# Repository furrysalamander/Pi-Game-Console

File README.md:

# Pi-Game-Console
 
A CM3+ Lite based handheld game console.

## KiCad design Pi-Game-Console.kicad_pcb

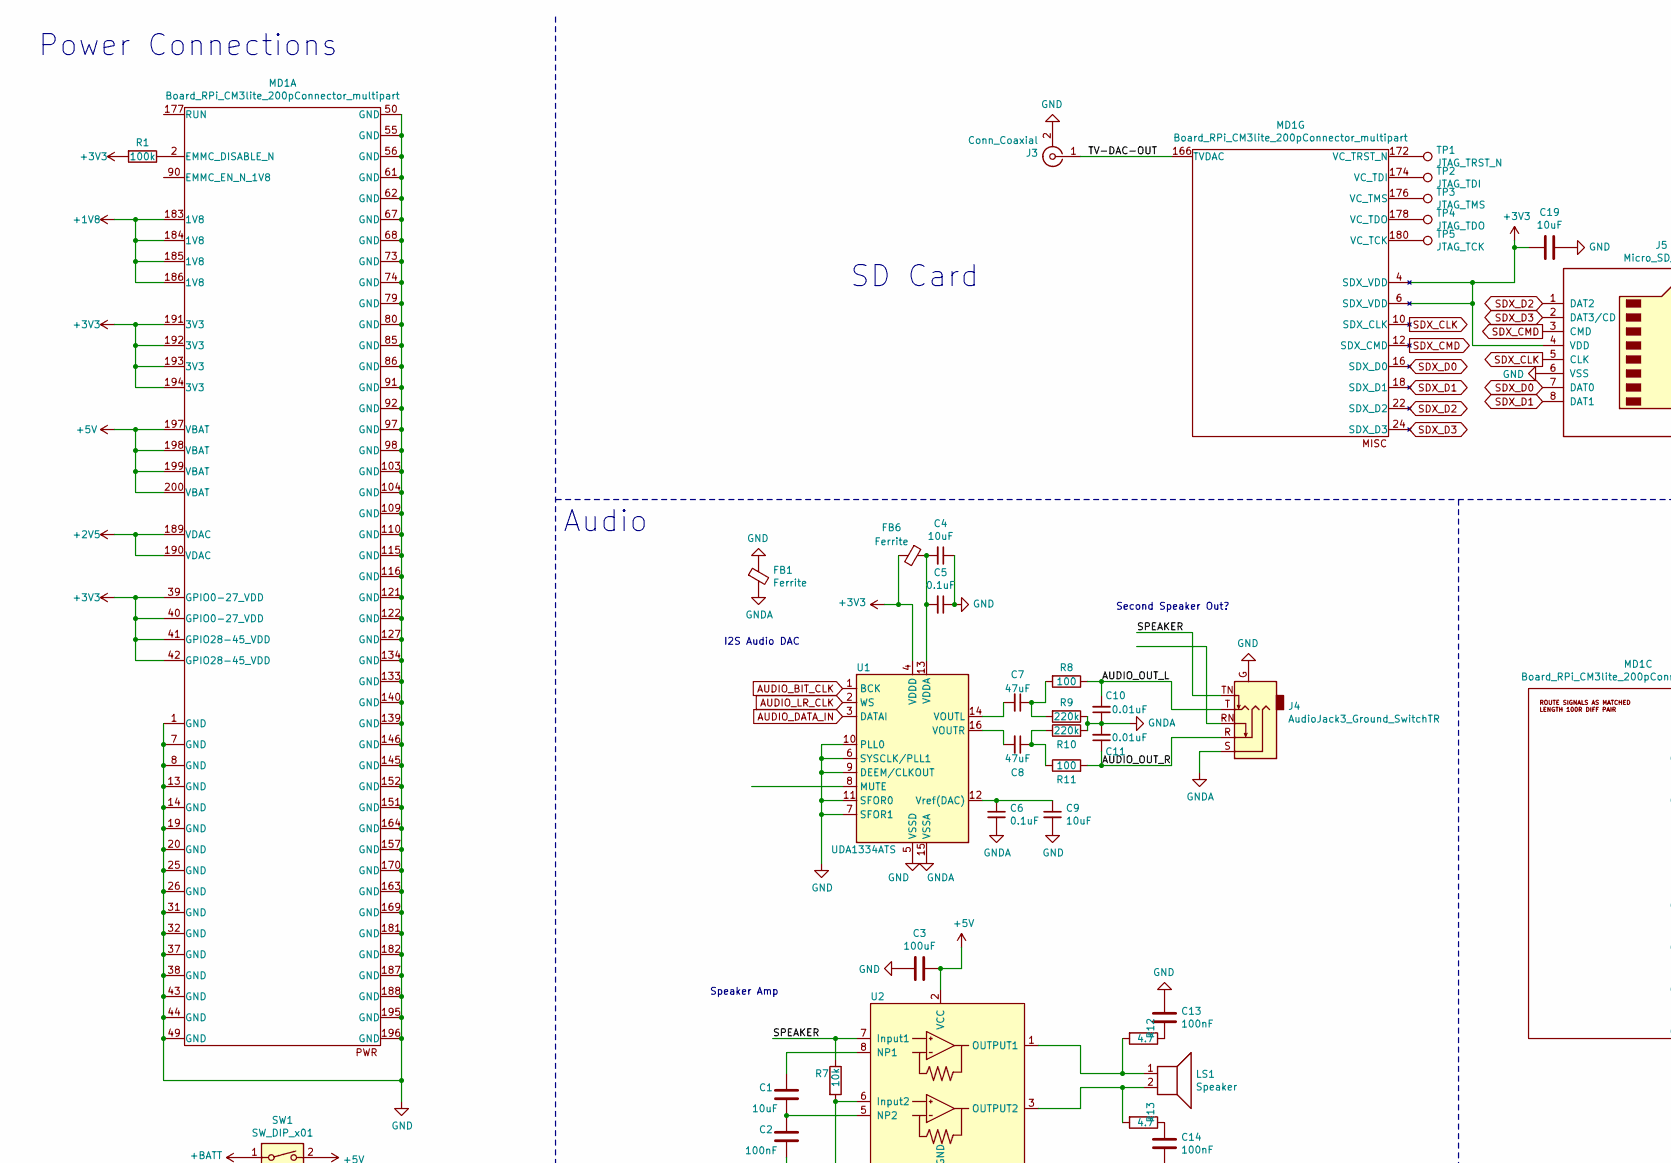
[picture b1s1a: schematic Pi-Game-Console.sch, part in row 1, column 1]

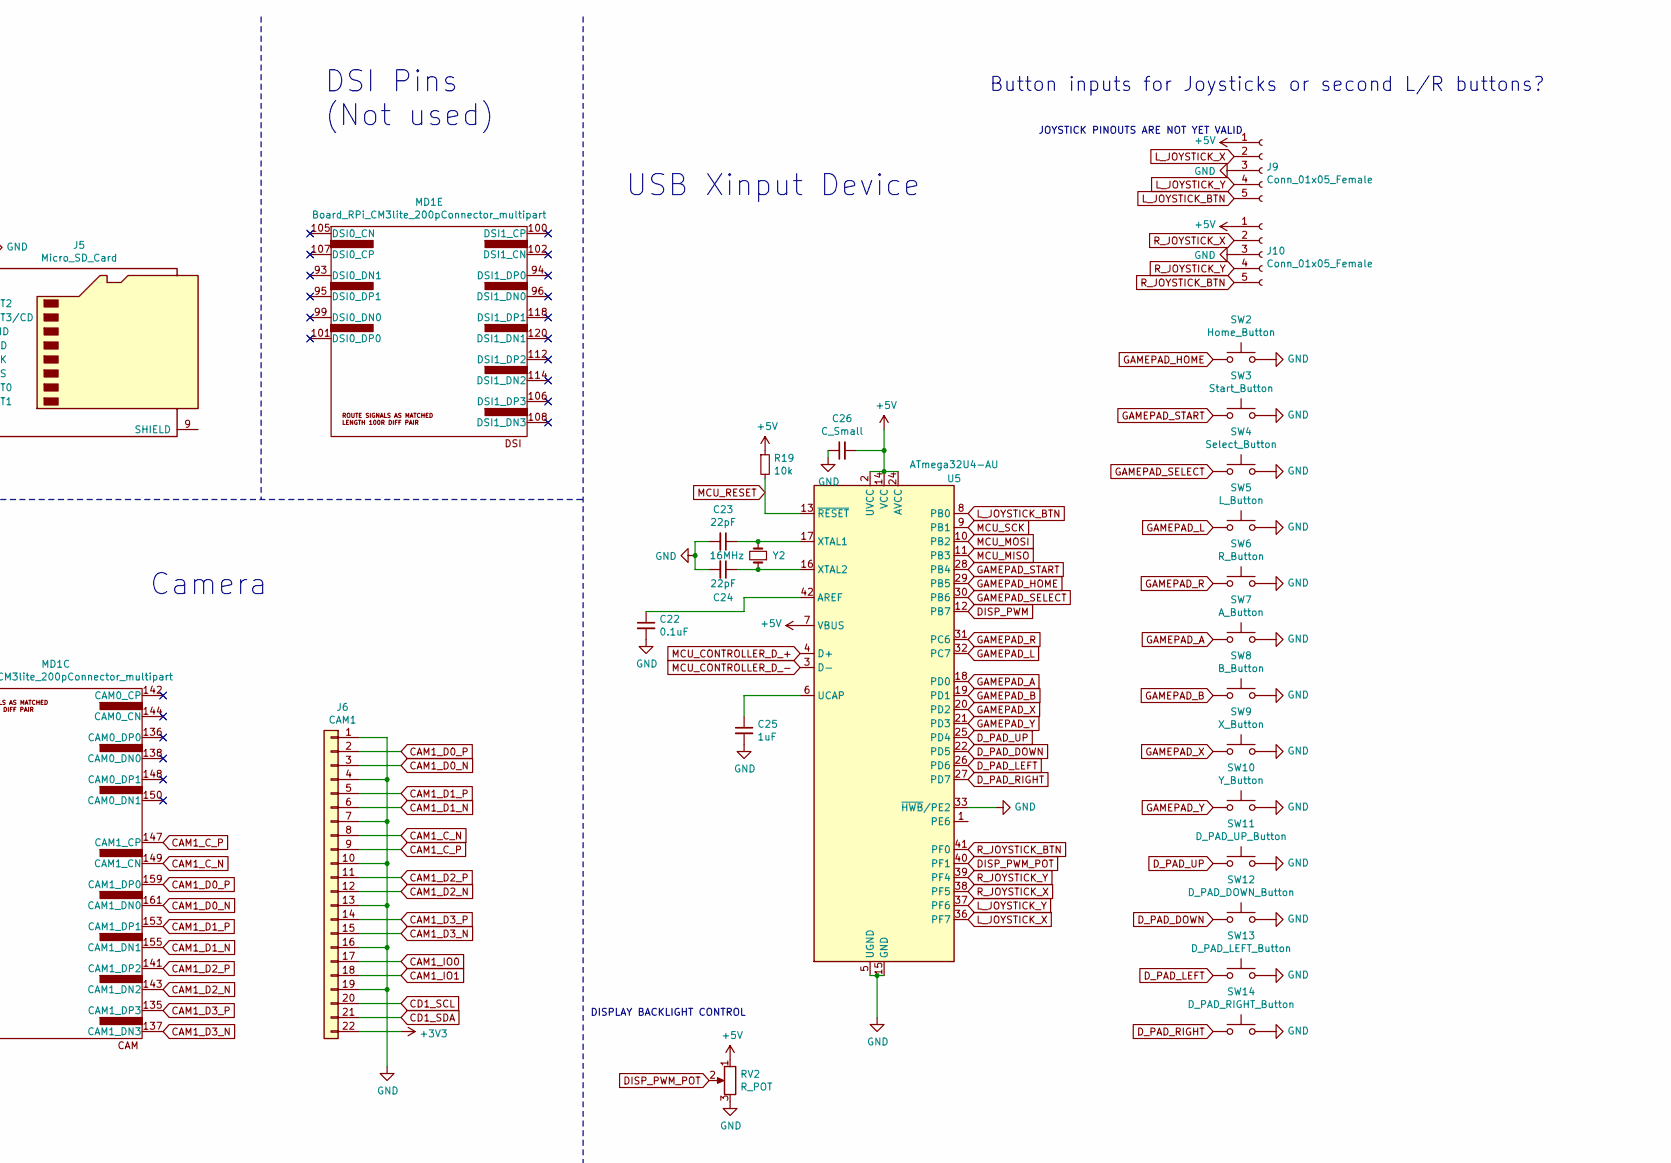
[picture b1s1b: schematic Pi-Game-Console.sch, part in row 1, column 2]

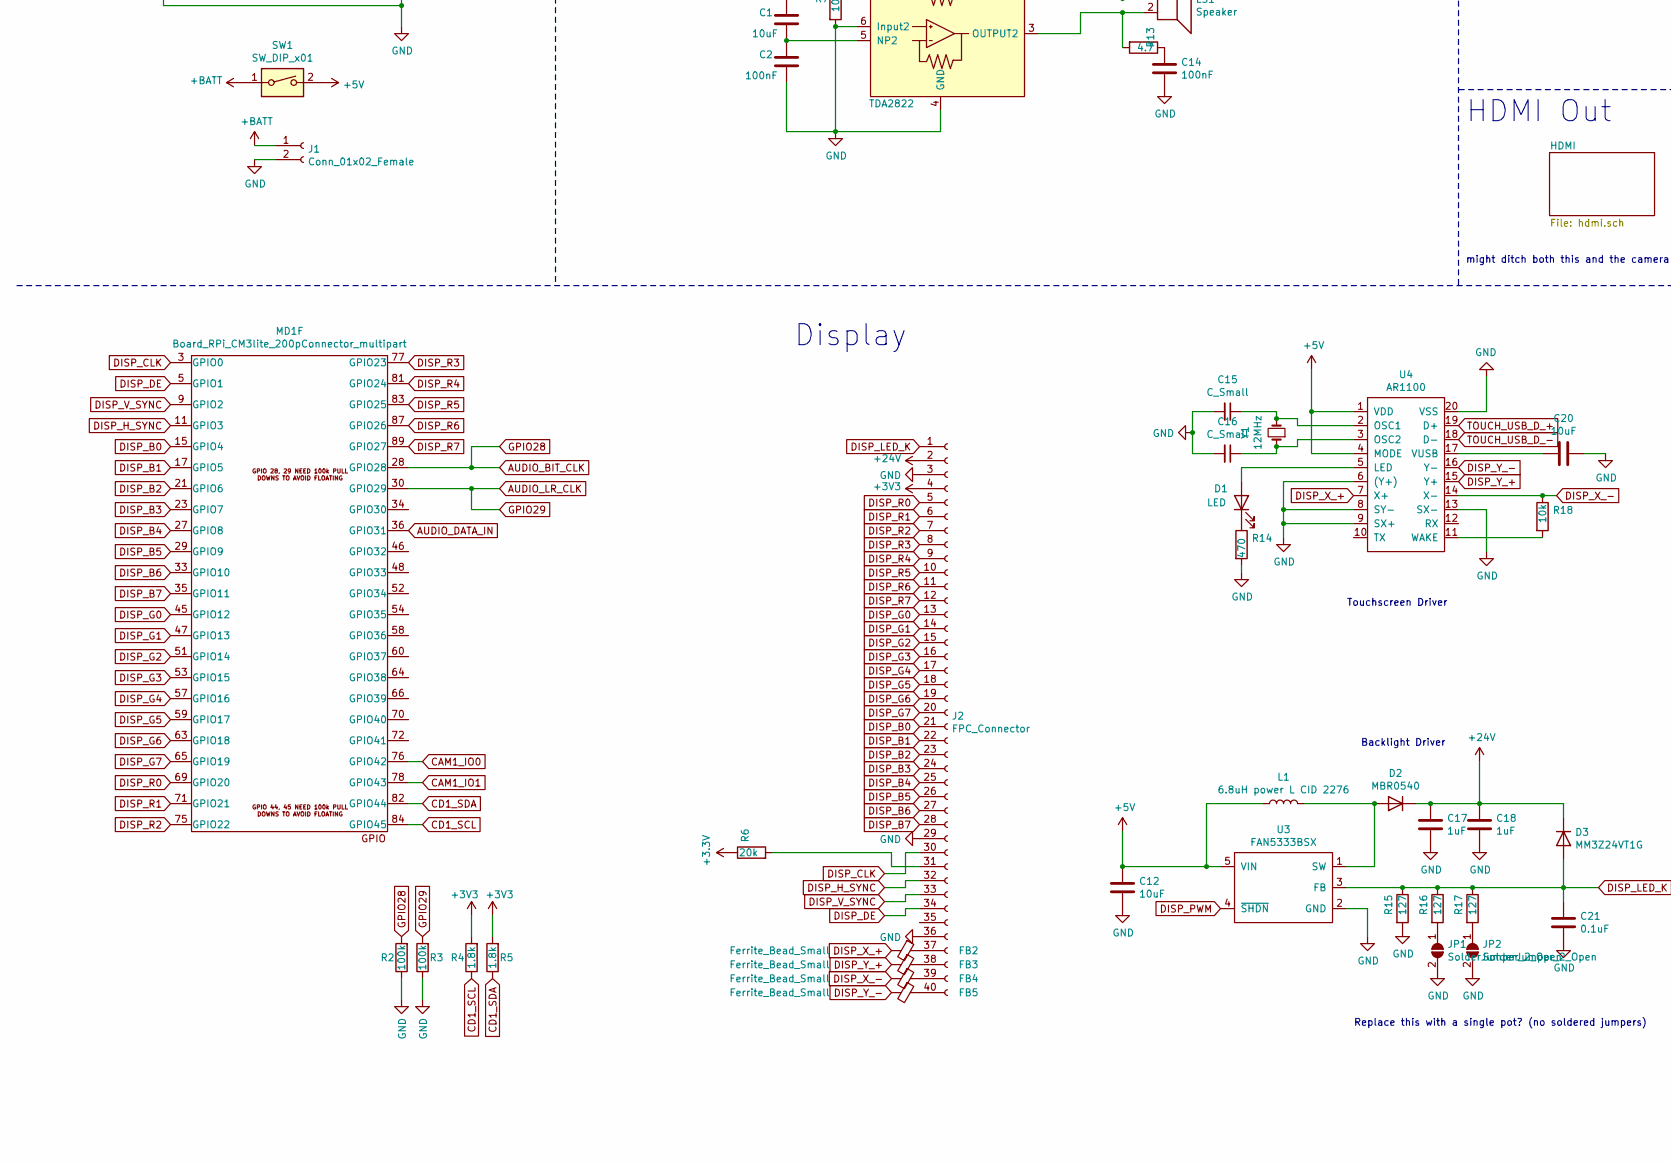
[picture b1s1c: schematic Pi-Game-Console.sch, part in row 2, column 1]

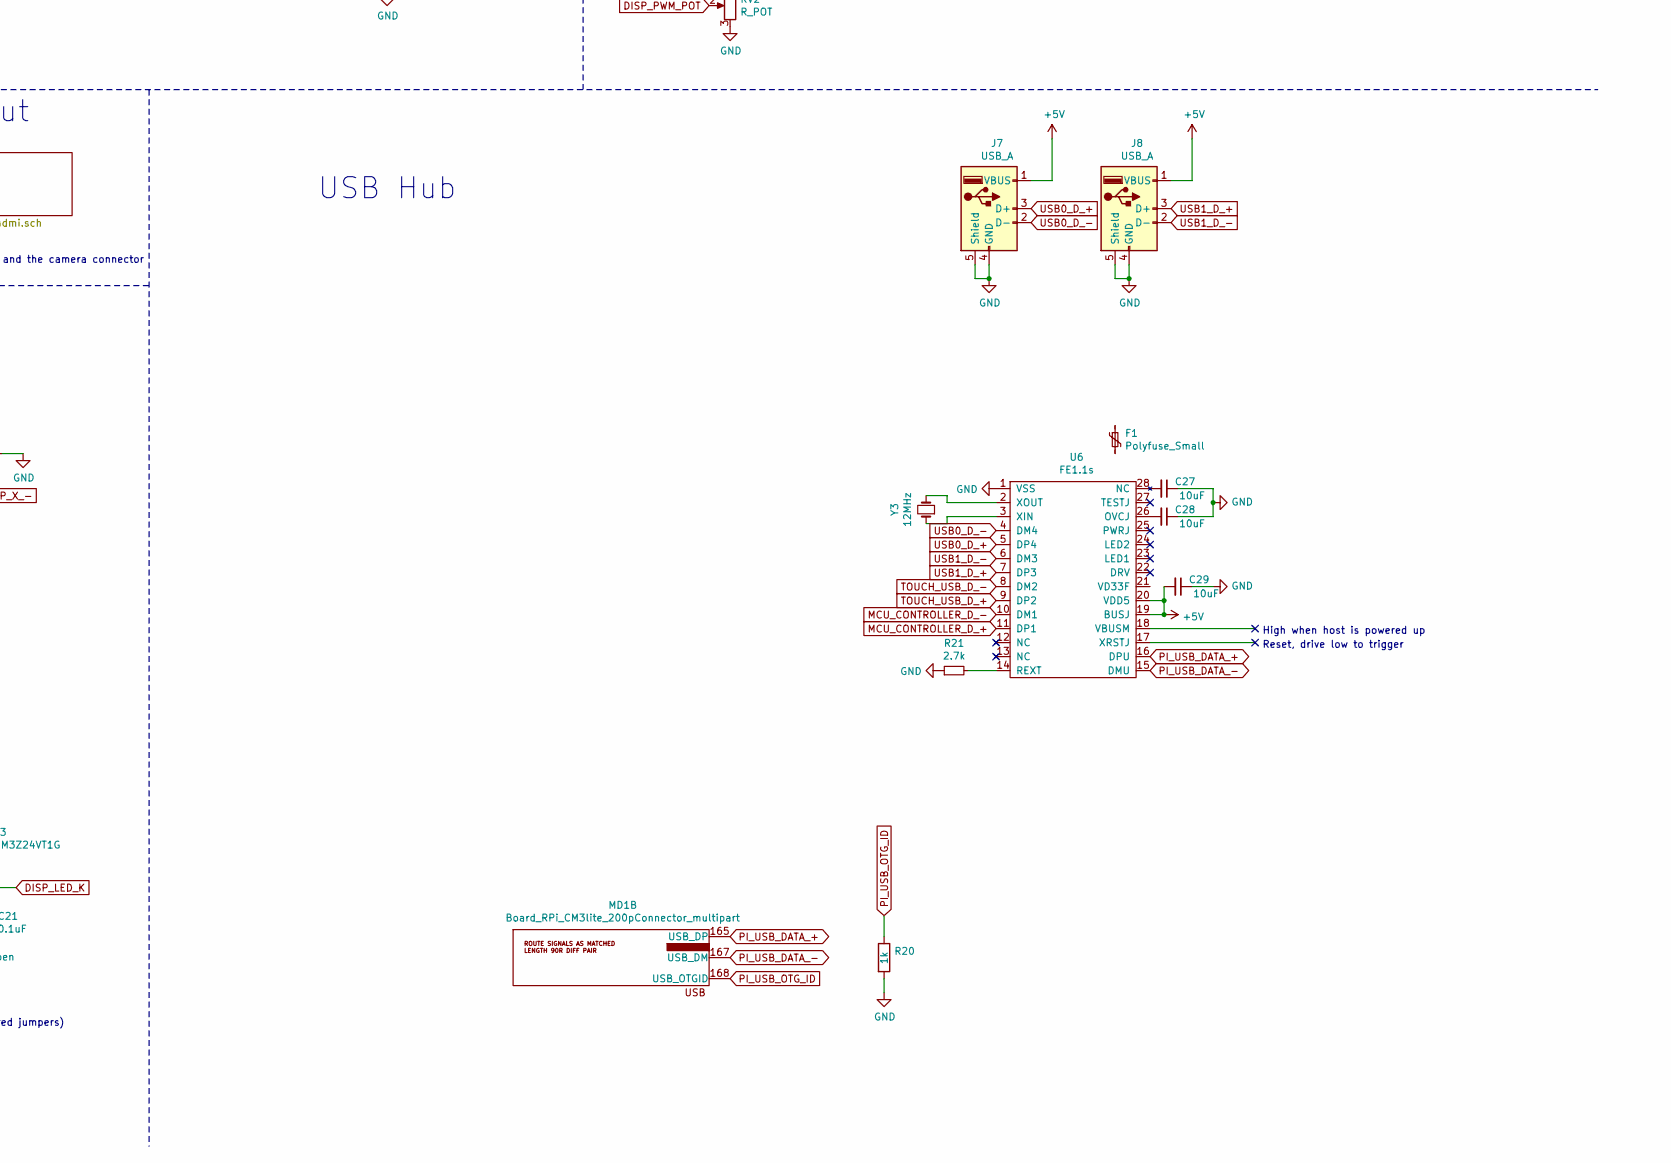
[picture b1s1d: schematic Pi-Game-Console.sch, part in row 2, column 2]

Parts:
C1, C4, C9, C12, C19, C20, C27, C28, C29: 10uF; C_0805_2012Metric
C2, C13, C14: 100nF; C_0805_2012Metric
C3: 100uF; C_0805_2012Metric
C5, C6, C21, C22: 0.1uF; C_0805_2012Metric
C7, C8: 47uF; C_0805_2012Metric
C10, C11: 0.01uF; C_0805_2012Metric
C15, C16, C26: C_Small; C_0805_2012Metric
C17, C18, C25: 1uF; C_0805_2012Metric
C23, C24: 22pF; C_0805_2012Metric
D1: LED; LED_0805_2012Metric
D2: MBR0540; D_0805_2012Metric
D3: MM3Z24VT1G; D_0805_2012Metric
F1: Polyfuse_Small; Littelfuse_PolyZen-LS
FB1, FB6: Ferrite; L_0805_2012Metric
FB2, FB3, FB4, FB5: Ferrite_Bead_Small; L_0805_2012Metric
J1: Conn_01x02_Female; PinHeader_1x02_P2.54mm_Vertical
J2: FPC_Connector; Hirose_FH12-40S-0.5SH_1x40-1MP_P0.50mm_Horizontal
J3: Conn_Coaxial; SMB_Jack_Vertical
J4: AudioJack3_Ground_SwitchTR; Jack_3.5mm_PJ311_Horizontal
J5: Micro_SD_Card; microSD_HC_Molex_104031-0811
J6: CAM1; Hirose_FH12-22S-0.5SH_1x22-1MP_P0.50mm_Horizontal
J7, J8: USB_A; USB_A_Stewart_SS-52100-001_Horizontal
J9, J10: Conn_01x05_Female; Molex_200528-0050_1x05-1MP_P1.00mm_Horizontal
JP1, JP2: SolderJumper_2_Open; SolderJumper-2_P1.3mm_Open_TrianglePad1.0x1.5mm
L1: 6.8uH power L CID 2276; L_Bourns-SRU1028_10.0x10.0mm
LS1: Speaker; Molex_CLIK-Mate_502382-0270_1x02-1MP_P1.25mm_Vertical
MD1: Board_RPi_CM3lite_200pConnector_multipart; Conn_TE-DDR2-SODIMM-0.6-200P-doublesided
R1, R2, R3: 100k; R_0805_2012Metric
R4, R5: 1.8k; R_0805_2012Metric
R6: 20k; R_0805_2012Metric
R7, R18, R19: 10k; R_0805_2012Metric
R8, R11: 100; R_0805_2012Metric
R9, R10: 220k; R_0805_2012Metric
R12, R13: 4.7; R_0805_2012Metric
R14: 470; R_0805_2012Metric
R15, R16, R17: 127; R_0805_2012Metric
R20: 1k; R_0805_2012Metric
R21: 2.7k; R_0805_2012Metric
RV2: R_POT; Potentiometer_Bourns_3269P_Horizontal
SW1: SW_DIP_x01; SW_CuK_OS102011MA1QN1_SPDT_Angled
SW2: Home_Button; SW_PUSH_6mm_H5mm
SW3: Start_Button; SW_PUSH_6mm_H5mm
SW4: Select_Button; SW_PUSH_6mm_H5mm
SW5: L_Button; SW_PUSH_6mm_H5mm
SW6: R_Button; SW_PUSH_6mm_H5mm
SW7: A_Button; SW_PUSH_6mm_H5mm
SW8: B_Button; SW_PUSH_6mm_H5mm
SW9: X_Button; SW_PUSH_6mm_H5mm
SW10: Y_Button; SW_PUSH_6mm_H5mm
SW11: D_PAD_UP_Button; SW_PUSH_6mm_H5mm
SW12: D_PAD_DOWN_Button; SW_PUSH_6mm_H5mm
SW13: D_PAD_LEFT_Button; SW_PUSH_6mm_H5mm
SW14: D_PAD_RIGHT_Button; SW_PUSH_6mm_H5mm
TP1: JTAG_TRST_N; TestPoint_Pad_D1.5mm
TP2: JTAG_TDI; TestPoint_Pad_D1.5mm
TP3: JTAG_TMS; TestPoint_Pad_D1.5mm
TP4: JTAG_TDO; TestPoint_Pad_D1.5mm
TP5: JTAG_TCK; TestPoint_Pad_D1.5mm
U1: UDA1334ATS; SSOP-16_4.4x5.2mm_P0.65mm
U2: TDA2822; SOIC-8_3.9x4.9mm_P1.27mm
U3: FAN5333BSX; SO-5_4.4x3.6mm_P1.27mm
U4: AR1100; SOIC-20W_7.5x12.8mm_P1.27mm
U5: ATmega32U4-AU; TQFP-44_10x10mm_P0.8mm
U6: FE1.1s; SOIC-28W_7.5x17.9mm_P1.27mm
Y1, Y3: 12MHz; Crystal_SMD_ECS_CSM3X-2Pin_7.6x4.1mm
Y2: 16MHz; Crystal_SMD_ECS_CSM3X-2Pin_7.6x4.1mm

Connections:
+1V8: MD1.183 (1V8), MD1.184 (1V8), MD1.185 (1V8), MD1.186 (1V8)
+2V5: MD1.189 (VDAC), MD1.190 (VDAC)
+5V: C3.2, C12.1, C26.2, C29.2, J7.1 (VBUS), J8.1 (VBUS), J9.1, J10.1, L1.1, MD1.197 (VBAT), MD1.198 (VBAT), MD1.199 (VBAT), MD1.200 (VBAT), R19.1, RV2.1, SW1.2, U2.2 (VCC), U3.5 (VIN), U4.1 (VDD), U4.4 (MODE), U5.2 (UVCC), U5.7 (VBUS), U5.14 (VCC), U5.24 (AVCC), U5.34 (VCC), U5.44 (AVCC), U6.19 (BUSJ), U6.20 (VDD5); also elsewhere on the board
+24V: C17.1, C18.1, D2.1 (K), D3.1 (K), J2.2
+BATT: J1.1, SW1.1
/AUDIO_OUT_L: C10.2, J4.T, R8.1
/AUDIO_OUT_R: C11.1, J4.R, R11.2
/SPEAKER: J4.TN, R7.1, U2.7 (Input1)
/TV-DAC-OUT: J3.1 (In), MD1.166 (TVDAC)
AUDIO_BIT_CLK: MD1.28 (GPIO28), R2.2, U1.1 (BCK)
AUDIO_DATA_IN: MD1.36 (GPIO31), U1.3 (DATAI)
AUDIO_LR_CLK: MD1.30 (GPIO29), R3.2, U1.2 (WS)
CAM1_C_N: J6.8, MD1.149 (CAM1_CN)
CAM1_C_P: J6.9, MD1.147 (CAM1_CP)
CAM1_D0_N: J6.3, MD1.161 (CAM1_DN0)
CAM1_D0_P: J6.2, MD1.159 (CAM1_DP0)
CAM1_D1_N: J6.6, MD1.155 (CAM1_DN1)
CAM1_D1_P: J6.5, MD1.153 (CAM1_DP1)
CAM1_D2_N: J6.12, MD1.143 (CAM1_DN2)
CAM1_D2_P: J6.11, MD1.141 (CAM1_DP2)
CAM1_D3_N: J6.15, MD1.137 (CAM1_DN3)
CAM1_D3_P: J6.14, MD1.135 (CAM1_DP3)
CAM1_IO0: J6.17, MD1.76 (GPIO42)
CAM1_IO1: J6.18, MD1.78 (GPIO43)
CD1_SCL: J6.20, MD1.84 (GPIO45), R4.1
CD1_SDA: J6.21, MD1.82 (GPIO44), R5.1
DISP_B0: J2.21, MD1.15 (GPIO4)
DISP_B1: J2.22, MD1.17 (GPIO5)
DISP_B2: J2.23, MD1.21 (GPIO6)
DISP_B3: J2.24, MD1.23 (GPIO7)
DISP_B4: J2.25, MD1.27 (GPIO8)
DISP_B5: J2.26, MD1.29 (GPIO9)
DISP_B6: J2.27, MD1.33 (GPIO10)
DISP_B7: J2.28, MD1.35 (GPIO11)
DISP_CLK: J2.30, MD1.3 (GPIO0)
DISP_DE: J2.34, MD1.5 (GPIO1)
DISP_G0: J2.13, MD1.45 (GPIO12)
DISP_G1: J2.14, MD1.47 (GPIO13)
DISP_G2: J2.15, MD1.51 (GPIO14)
DISP_G3: J2.16, MD1.53 (GPIO15)
DISP_G4: J2.17, MD1.57 (GPIO16)
DISP_G5: J2.18, MD1.59 (GPIO17)
DISP_G6: J2.19, MD1.63 (GPIO18)
DISP_G7: J2.20, MD1.65 (GPIO19)
DISP_H_SYNC: J2.32, MD1.11 (GPIO3)
DISP_LED_K: C21.1, D3.2 (A), J2.1, R15.1, R16.1, R17.1, U3.3 (FB); also elsewhere on the board
DISP_PWM: U3.4 (~SHDN), U5.12 (PB7)
DISP_PWM_POT: RV2.2, U5.40 (PF1)
DISP_R0: J2.5, MD1.69 (GPIO20)
DISP_R1: J2.6, MD1.71 (GPIO21)
DISP_R2: J2.7, MD1.75 (GPIO22)
DISP_R3: J2.8, MD1.77 (GPIO23)
DISP_R4: J2.9, MD1.81 (GPIO24)
DISP_R5: J2.10, MD1.83 (GPIO25)
DISP_R6: J2.11, MD1.87 (GPIO26)
DISP_R7: J2.12, MD1.89 (GPIO27)
DISP_V_SYNC: J2.33, MD1.9 (GPIO2)
DISP_X_+: FB2.2, U4.7 (X+)
DISP_X_-: FB4.2, R18.1, U4.14 (X-)
DISP_Y_+: FB3.2, U4.15 (Y+)
DISP_Y_-: FB5.2, U4.16 (Y-)
D_PAD_DOWN: SW12.1, U5.22 (PD5)
D_PAD_LEFT: SW13.1, U5.26 (PD6)
D_PAD_RIGHT: SW14.1, U5.27 (PD7)
D_PAD_UP: SW11.1, U5.25 (PD4)
GAMEPAD_A: SW7.1, U5.18 (PD0)
GAMEPAD_B: SW8.1, U5.19 (PD1)
GAMEPAD_HOME: SW2.1, U5.29 (PB5)
GAMEPAD_L: SW5.1, U5.32 (PC7)
GAMEPAD_R: SW6.1, U5.31 (PC6)
GAMEPAD_SELECT: SW4.1, U5.30 (PB6)
GAMEPAD_START: SW3.1, U5.28 (PB4)
GAMEPAD_X: SW9.1, U5.20 (PD2)
GAMEPAD_Y: SW10.1, U5.21 (PD3)
GND: C2.2, C3.1, C4.1, C5.1, C9.2, C12.2, C13.1, C14.2, C15.2, C16.2, C17.2, C18.2, C19.2, C20.1, C21.2, C22.2, C23.2, C24.2, C25.2, C26.1, C27.1, C28.1, C29.1, FB1.1, J1.2, J2.3, J2.29, J2.36, J3.2 (Ext), J4.G, J5.6 (VSS), J6.1, J6.4, J6.7, J6.10, J6.13, J6.16, J6.19, J7.4 (GND), J7.5 (Shield), J8.4 (GND), J8.5 (Shield), J9.3, J10.3, JP1.2 (B), JP2.2 (B), MD1.1 (GND), MD1.7 (GND), MD1.8 (GND), MD1.13 (GND), MD1.14 (GND), MD1.19 (GND), MD1.20 (GND), MD1.25 (GND), MD1.26 (GND), MD1.31 (GND), MD1.32 (GND), MD1.37 (GND), MD1.38 (GND), MD1.43 (GND), MD1.44 (GND), MD1.49 (GND), MD1.50 (GND), MD1.55 (GND), MD1.56 (GND), MD1.61 (GND), MD1.62 (GND), MD1.67 (GND), MD1.68 (GND), MD1.73 (GND), MD1.74 (GND), MD1.79 (GND), MD1.80 (GND), MD1.85 (GND), MD1.86 (GND), MD1.91 (GND), MD1.92 (GND), MD1.97 (GND), MD1.98 (GND), MD1.103 (GND), MD1.104 (GND), MD1.109 (GND), MD1.110 (GND), MD1.115 (GND), MD1.116 (GND), MD1.121 (GND), MD1.122 (GND), MD1.127 (GND), MD1.133 (GND), MD1.134 (GND), MD1.139 (GND), MD1.140 (GND), MD1.145 (GND), MD1.146 (GND), MD1.151 (GND), MD1.152 (GND), MD1.157 (GND), MD1.163 (GND), MD1.164 (GND), MD1.169 (GND), MD1.170 (GND), MD1.181 (GND), MD1.182 (GND), MD1.187 (GND), MD1.188 (GND), MD1.195 (GND), MD1.196 (GND), R2.1, R3.1, R7.2, R14.2, R15.2, R20.2, R21.1, RV2.3, SW2.2, SW3.2, SW4.2, SW5.2, SW6.2, SW7.2, SW8.2, SW9.2, SW10.2, SW11.2, SW12.2, SW13.2, SW14.2, U1.5 (VSSD), U1.6 (SYSCLK/PLL1), U1.7 (SFOR1), U1.9 (DEEM/CLKOUT), U1.10 (PLL0), U1.11 (SFOR0), U2.4 (GND), U2.6 (Input2), U3.2 (GND), U4.6 ((Y+)), U4.8 (SY-), U4.9 (SX+), U4.13 (SX-), U4.20 (VSS), U5.5 (UGND), U5.15 (GND), U5.23 (GND), U5.33 (~HWB~/PE2), U5.35 (GND), U5.43 (GND), U6.1 (VSS); also elsewhere on the board
GNDA: C6.2, C10.1, C11.2, FB1.2, J4.S, R9.1, R10.2, U1.15 (VSSA)
L_JOYSTICK_BTN: J9.5, U5.8 (PB0)
L_JOYSTICK_X: J9.2, U5.36 (PF7)
L_JOYSTICK_Y: J9.4, U5.37 (PF6)
MCU_CONTROLLER_D_+: U5.4 (D+), U6.11 (DP1)
MCU_CONTROLLER_D_-: U5.3 (D-), U6.10 (DM1)
MCU_MISO: U5.11 (PB3)
MCU_MOSI: U5.10 (PB2)
MCU_RESET: R19.2, U5.13 (~RESET)
MCU_SCK: U5.9 (PB1)
unnamed: C1.1, U2.8 (NP1)
unnamed: C1.2, C2.1, U2.5 (NP2)
unnamed: C4.2, C5.2, FB6.1, U1.13 (VDDA)
unnamed: C6.1, C9.1, U1.12 (Vref(DAC))
unnamed: C7.1, R8.2, R9.2
unnamed: C7.2, U1.14 (VOUTL)
unnamed: C8.1, R10.1, R11.1
unnamed: C8.2, U1.16 (VOUTR)
unnamed: C13.2, R12.1
unnamed: C14.1, R13.1
unnamed: C15.1, U4.2 (OSC1), Y1.2
unnamed: C16.1, U4.3 (OSC2), Y1.1
unnamed: C20.2, U4.17 (VUSB)
unnamed: C22.1, U5.42 (AREF)
unnamed: C23.1, U5.17 (XTAL1), Y2.2
unnamed: C24.1, U5.16 (XTAL2), Y2.1
unnamed: C25.1, U5.6 (UCAP)
unnamed: C27.2, U6.28 (NC)
unnamed: C28.2, U6.26 (OVCJ)
unnamed 117: D1.1 (K), R14.1; also elsewhere on the board
unnamed 118: D1.2 (A), U4.5 (LED); also elsewhere on the board
unnamed: D2.2 (A), L1.2, U3.1 (SW)
unnamed: FB2.1, J2.37
unnamed: FB3.1, J2.38
unnamed: FB4.1, J2.39
unnamed: FB5.1, J2.40
unnamed: J2.31, R6.2
unnamed: JP1.1 (A), R16.2
unnamed 133: JP2.1 (A), R17.2; also elsewhere on the board
unnamed: LS1.1, R12.2, U2.1 (OUTPUT1)
unnamed: LS1.2, R13.2, U2.3 (OUTPUT2)
unnamed: MD1.2 (EMMC_DISABLE_N), R1.1
unnamed: MD1.172 (VC_TRST_N), TP1.1
unnamed: MD1.174 (VC_TDI), TP2.1
unnamed: MD1.176 (VC_TMS), TP3.1
unnamed: MD1.178 (VC_TDO), TP4.1
unnamed: MD1.180 (VC_TCK), TP5.1
unnamed: R18.2, U4.11 (WAKE)
unnamed: R21.2, U6.14 (REXT)
unnamed: U6.2 (XOUT), Y3.2
unnamed: U6.3 (XIN), Y3.1
PI_USB_DATA_+: MD1.165 (USB_DP), U6.16 (DPU)
PI_USB_DATA_-: MD1.167 (USB_DM), U6.15 (DMU)
PI_USB_OTG_ID: MD1.168 (USB_OTGID), R20.1
R_JOYSTICK_BTN: J10.5, U5.41 (PF0)
R_JOYSTICK_X: J10.2, U5.38 (PF5)
R_JOYSTICK_Y: J10.4, U5.39 (PF4)
SDX_CLK: J5.5 (CLK), MD1.10 (SDX_CLK)
SDX_CMD: J5.3 (CMD), MD1.12 (SDX_CMD)
SDX_D0: J5.7 (DAT0), MD1.16 (SDX_D0)
SDX_D1: J5.8 (DAT1), MD1.18 (SDX_D1)
SDX_D2: J5.1 (DAT2), MD1.22 (SDX_D2)
SDX_D3: J5.2 (DAT3/CD), MD1.24 (SDX_D3)
TOUCH_USB_D_+: U4.19 (D+), U6.9 (DP2)
TOUCH_USB_D_-: U4.18 (D-), U6.8 (DM2)
USB0_D_+: J7.3 (D+), U6.5 (DP4)
USB0_D_-: J7.2 (D-), U6.4 (DM4)
USB1_D_+: J8.3 (D+), U6.7 (DP3)
USB1_D_-: J8.2 (D-), U6.6 (DM3)

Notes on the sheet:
Reset, drive low to trigger
High when host is powered up
Audio
Replace this with a single pot? (no soldered jumpers)
Button inputs for Joysticks or second L/R buttons?
Power Connections
Display
SD Card
Camera
USB Hub
USB Xinput Device
DSI Pins (Not used)
HDMI Out
Touchscreen Driver
Backlight Driver
might ditch both this and the camera connector
Speaker Amp
I2S Audio DAC
Second Speaker Out?
JOYSTICK PINOUTS ARE NOT YET VALID
DISPLAY BACKLIGHT CONTROL

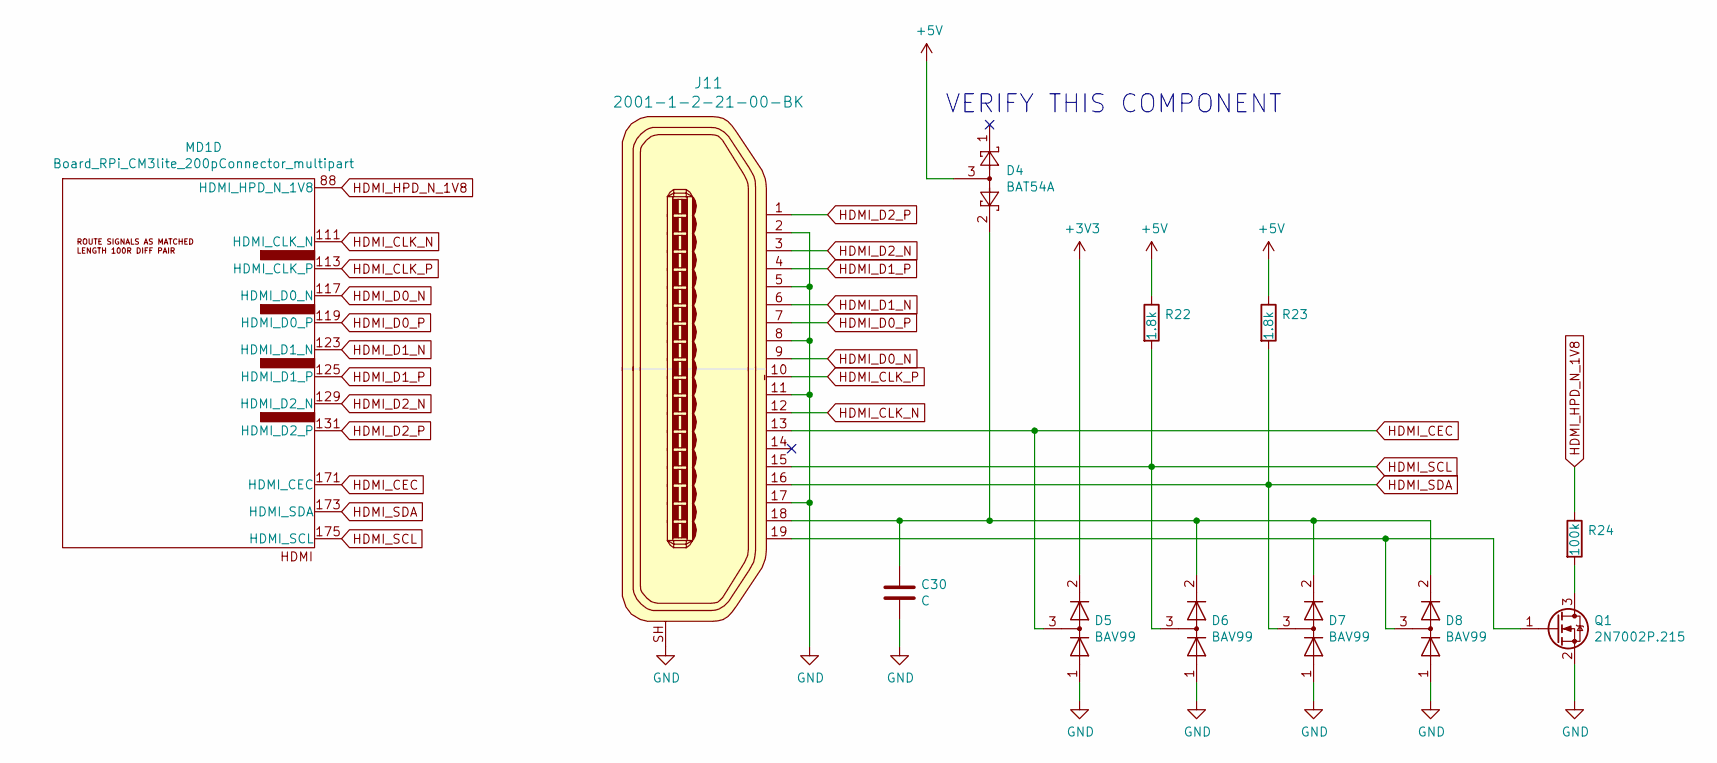
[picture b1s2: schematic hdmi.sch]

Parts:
C30: C; C_0805_2012Metric
D4: BAT54A; SOT-23
D5, D6, D7, D8: BAV99; SOT-23
J11: 2001-1-2-21-00-BK; HDMI_MOLEX_471510001; MPN 2001-1-2-21-00-BK; Digi-Key_PN 1175-1704-1-ND
MD1: Board_RPi_CM3lite_200pConnector_multipart; Conn_TE-DDR2-SODIMM-0.6-200P-doublesided
Q1: 2N7002P.215; SOT-23
R22, R23: 1.8k; R_0805_2012Metric
R24: 100k; R_0805_2012Metric

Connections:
+5V: D4.3, R22.1, R23.1; also elsewhere on the board
GND: C30.2, D5.1 (K), D6.1 (K), D7.1 (K), D8.1 (K), J11.2, J11.5, J11.8, J11.11, J11.17, J11.SH, Q1.2 (S); also elsewhere on the board
HDMI_CEC: D5.3 (K), J11.13, MD1.171 (HDMI_CEC)
HDMI_CLK_N: J11.12, MD1.111 (HDMI_CLK_N)
HDMI_CLK_P: J11.10, MD1.113 (HDMI_CLK_P)
HDMI_D0_N: J11.9, MD1.117 (HDMI_D0_N)
HDMI_D0_P: J11.7, MD1.119 (HDMI_D0_P)
HDMI_D1_N: J11.6, MD1.123 (HDMI_D1_N)
HDMI_D1_P: J11.4, MD1.125 (HDMI_D1_P)
HDMI_D2_N: J11.3, MD1.129 (HDMI_D2_N)
HDMI_D2_P: J11.1, MD1.131 (HDMI_D2_P)
HDMI_HPD_N_1V8: MD1.88 (HDMI_HPD_N_1V8), R24.1
HDMI_SCL: D6.3 (K), J11.15, MD1.175 (HDMI_SCL), R22.2
HDMI_SDA: D7.3 (K), J11.16, MD1.173 (HDMI_SDA), R23.2
unnamed: C30.1, D4.2, D6.2 (A), D7.2 (A), D8.2 (A), J11.18
unnamed: D8.3 (K), J11.19, Q1.1 (G)
unnamed: Q1.3 (D), R24.2

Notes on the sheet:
VERIFY THIS COMPONENT

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
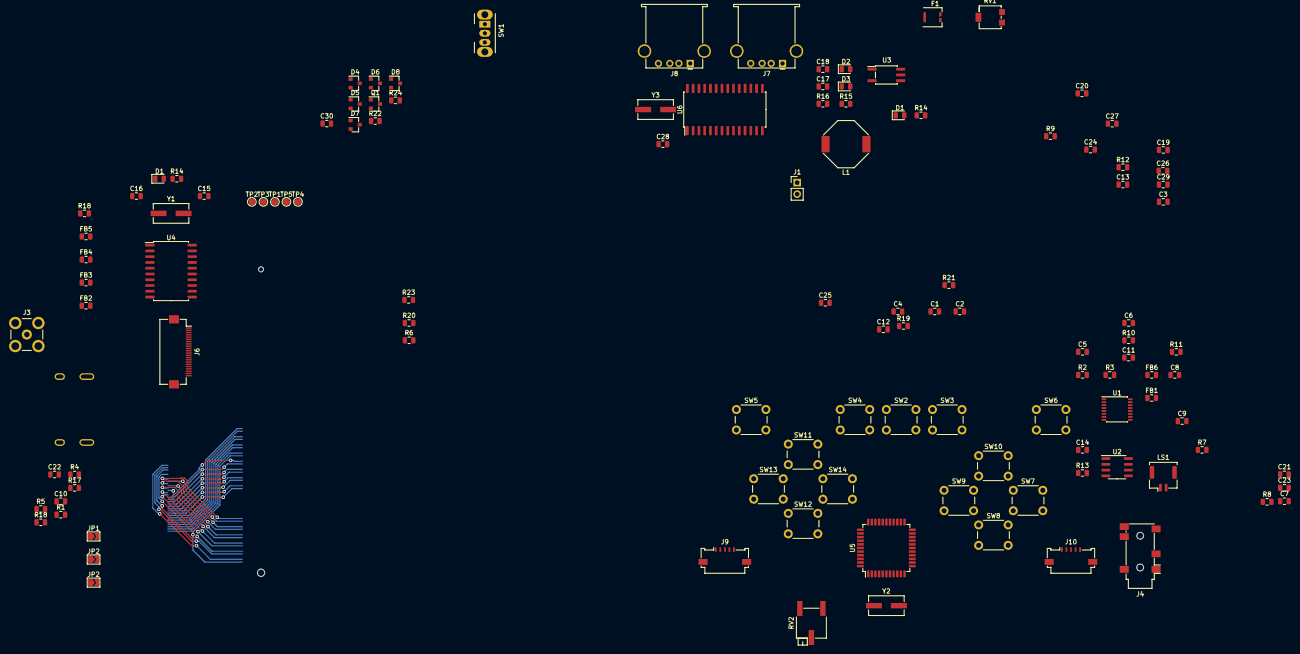
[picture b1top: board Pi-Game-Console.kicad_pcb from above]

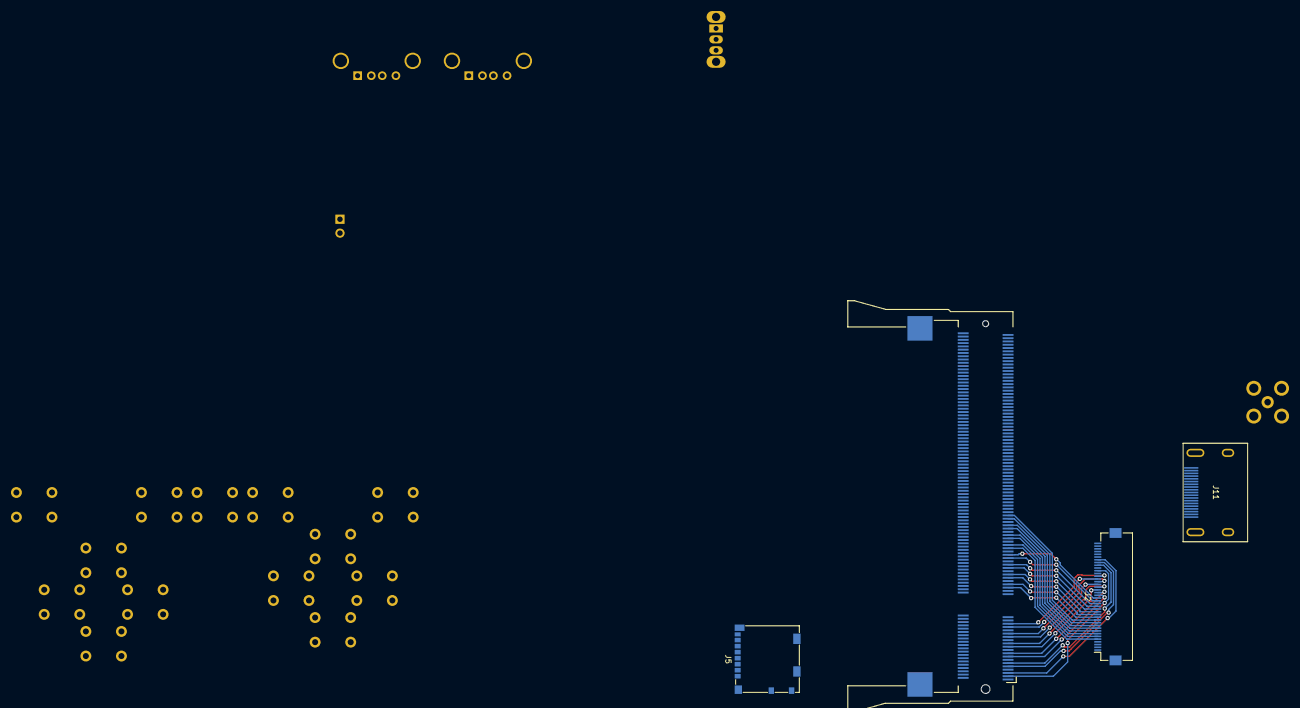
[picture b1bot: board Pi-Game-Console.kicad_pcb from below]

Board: 2 copper layers, 120 parts (4 on the bottom side), 157 nets.

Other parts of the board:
D1#2: 1N4148; D_0805_2012Metric
JP2#2: SolderJumper_2_Open; SolderJumper-2_P1.3mm_Open_TrianglePad1.0x1.5mm
R14#2: 20k; R_0805_2012Metric
R18#2: 67; R_0805_2012Metric
RV1: R_POT; Potentiometer_Bourns_3214G_Horizontal

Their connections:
+5V: R14#2.1; also elsewhere on the board
DISP_LED_K: R18#2.1; also elsewhere on the board
GND: JP2#2.2; also elsewhere on the board
unnamed 117: D1#2.1; also elsewhere on the board
unnamed 118: D1#2.2, R14#2.2; also elsewhere on the board
unnamed 133: JP2#2.1, R18#2.2; also elsewhere on the board

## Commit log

2020-02-06 Ditching HDMI
    Looks like we can't have DPI and HDMI enabled at the same time. With that being the case, I'm not going to deal with all the components needed to add HDMI output.
2020-02-08 Added usb gamepad and new hub
2020-02-08 Added HDMI and Audio Circuit
    Still need to verify a few components for the HDMI connector. Also, the Audio is only headphone out right now. I still need to wire up the speaker and make it automaticaly switch. Just need to do som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
2020-02-08 Wired up the DPI display and Camera
    Still need to wire up the DPI connector.
2020-02-09 minor updates
2020-02-09 Added USB Ports and wired up more of the DPI connector
2020-02-10 Cleaned up schematic
2020-02-10 Added documentation
2020-02-10 Switched Audio Circuit to use Retro-CM3 Schematic
2020-02-11 Removed Second USB Hub
    Also wired up a few more connections.
2020-02-11 Updated the audio generation to use I2S
2020-02-11 Removed resistor arrays feeding into display
    I really don't know that they're necessary, since the TFT friend from Adafruit doesn't have them, and they drive up the component count a fair amount. Plus they're a real pain to solder. If we change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
2020-02-12 minor changes
2020-02-12 updated display traces.
2020-02-13 Fixed footprints, added PWM to display backlight
2020-02-14 Added Buck Converters for Power
2020-02-18 Updated values for several parts
    Mostly capacitors. Still need to do further review the schematic before it's all the way finished.
2020-02-20 Added more part values
